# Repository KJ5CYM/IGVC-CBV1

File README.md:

# IGVC-CBV1
This is a failed project! The board as it stands does not work, due to my own amateur mistakes.

This board is the first step in a project to replace Arduino with custom hardware on the robot for the UT IGVC Team.
 
# Original Designers and Developers (2023)
Evan Eden, Colby McLane, Kerwin Zhang, Tarun Daggolu.

# Updates
Firmware is in developement and should surface within the coming weeks.

# 3D - View

# PCB

# Schematic

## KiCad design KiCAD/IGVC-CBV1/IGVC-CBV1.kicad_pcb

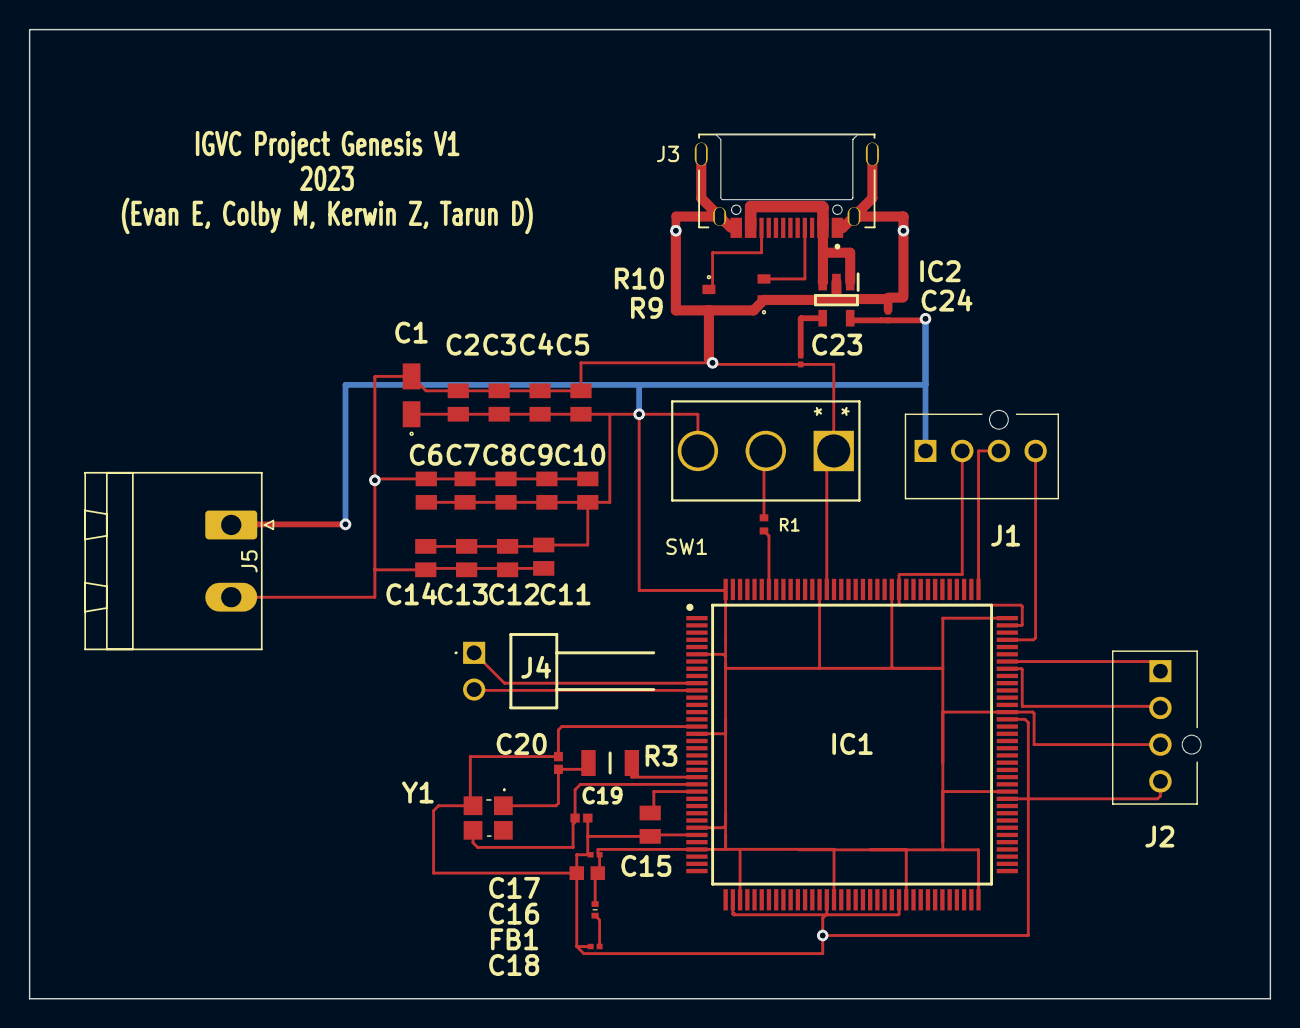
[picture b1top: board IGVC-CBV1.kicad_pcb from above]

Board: 2 copper layers, 85.9 x 67.1 mm, 36 parts (0 on the bottom side), 18 nets.

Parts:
C1: 10u; T491A
C2, C3, C4, C5, C6, C7, C8, C9, C10, C11, C12, C13, C14, C15: 100n; CAPC2012X140N
C16: 10n; CAPC17595_87N_KEM
C17, C18: 1u; CAPC0502X28N
C19, C20: 12 pF; CAPC1005X55N
C23: 1uF; CAPC0502X28N
C24: 1 uF; CAPC0502X28N
FB1: 120R; NFZ15SG152SN10B
IC1: STM32F407ZGT6; QFP50P2200X2200X160-144N
IC2: SPX3819M5-L-3-3_TR; SOT95P280X145-5N
J1: STLINKV2 PINS (2.54mm Pitch); 470531000
J2: Motor Driver Pins (2.54mm Pitch); 470531000
J3: 12401948E412A; AMPHENOL_12401948E412A
J4: Conn_01x02; 22122024
J5: Screw_Terminal_01x02; PhoenixContact_MSTBA_2,5_2-G_1x02_P5.00mm_Horizontal
R1: 10k; RESC1005X40N
R3: 60 Ohm; RESC3216X60N
R9, R10: 5K1; ERA3KV__0603_
SW1: SW_SPDT; 1101M2S3CQE2
Y1: EB2532YA12-25.000M_TR; EB2532YA1225000MTR

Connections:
+3.3V: C1.1, C2.1, C3.1, C4.1, C5.1, C6.1, C7.1, C8.1, C9.1, C10.1, C11.1, C12.1, C13.1, C14.1, C16.1, C17.1, C18.1, C24.1, FB1.1, FB1.2, IC1.6 (VBAT), IC1.17 (VDD_1), IC1.30 (VDD_2), IC1.33 (VDDA), IC1.39 (VDD_3), IC1.52 (VDD_4), IC1.62 (VDD_5), IC1.72 (VDD_6), IC1.84 (VDD_7), IC1.95 (VDD_8), IC1.108 (VDD_9), IC1.121 (VDD_10), IC1.131 (VDD_11), IC1.144 (VDD_12), IC2.5 (VOUT), J1.1, J2.3, J5.1, SW1.3 (C)
/BOOT0: IC1.138 (BOOT0), R1.2
/NRST: C15.1, IC1.25 (NRST)
/SW_BOOT0: R1.1, SW1.2 (B)
GND: C1.2, C2.2, C3.2, C4.2, C5.2, C6.2, C7.2, C8.2, C9.2, C10.2, C11.2, C12.2, C13.2, C14.2, C15.2, C16.2, C17.2, C18.2, C19.1, C20.1, C23.1, C24.2, IC1.16 (VSS_1), IC1.31 (VSSA), IC1.38 (VSS_2), IC1.51 (VSS_3), IC1.61 (VSS_4), IC1.83 (VSS_5), IC1.94 (VSS_6), IC1.107 (VSS_7), IC1.120 (VSS_8), IC1.130 (VSS_9), IC2.2 (GND), J1.2, J2.4, J3.A1_B12 (GND), J3.A12_B1 (GND), J3.S1 (SHELL_GND), J3.S2 (SHELL_GND), J3.S3 (SHELL_GND), J3.S4 (SHELL_GND), J5.2, R9.1, R10.2, SW1.1 (A), Y1.2 (COVER/GROUND)
I2C2_SCL: IC1.11 (PF1), J4.2
I2C2_SDA: IC1.10 (PF0), J4.1
unnamed: C23.2, IC2.4 (ADJ/BYP)
unnamed: J3.A5 (CC1), R9.2
unnamed: J3.B5 (CC2), R10.1
unnamed: C20.2, R3.1, Y1.1 (CRYSTAL_1)
RCC_OSC_IN: IC1.23 (PH0), R3.2
RCC_OSC_OUT: C19.2, IC1.24 (PH1), Y1.3 (CRYSTAL_2)
SWCLK: IC1.109 (PA14), J1.3
SWDIO: IC1.105 (PA13), J1.4
USART1_RX: IC1.102 (PA10), J2.1
USART1_TX: IC1.101 (PA9), J2.2
VBUS: IC2.1 (VIN), IC2.3 (EN), J3.A4_B9 (VBUS), J3.A9_B4 (VBUS)

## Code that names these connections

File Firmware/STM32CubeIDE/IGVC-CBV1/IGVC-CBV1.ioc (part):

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Mcu.Name=STM32F407Z(E-G)Tx
Mcu.Package=LQFP144
Mcu.UserName=STM32F407ZGTx
PA10.Mode=Asynchronous
PA10.Signal=USART1_RX
PA13.Mode=Serial_Wire
PA13.Signal=SYS_JTMS-SWDIO
PA14.Mode=Serial_Wire
PA14.Signal=SYS_JTCK-SWCLK
PA9.Mode=Asynchronous
PA9.Signal=USART1_TX
PF0.Mode=I2C
PF0.Signal=I2C2_SDA
PF1.Mode=I2C
PF1.Signal=I2C2_SCL
PH0-OSC_IN.Mode=HSE-External-Oscillator
PH0-OSC_IN.Signal=RCC_OSC_IN
PH1-OSC_OUT.Mode=HSE-External-Oscillator
PH1-OSC_OUT.Signal=RCC_OSC_OUT
RCC.HSE_VALUE=25000000
RCC.SYSCLKFreq_VALUE=168000000
RCC.SYSCLKSource=RCC_SYSCLKSOURCE_PLLCLK
board=custom

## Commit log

2023-09-29 Added initial schematic with cursed power setup
2023-09-29 STM32 symbol
2023-09-30 Cleaned up and have a basis for pin functions.
2023-10-01 Implemented Clock and STLink Header
    Also, defined our potential pins on the controller for I2C, UART, and such.
2023-10-03 8MB NOR Flash added to schematic with associated docs and files
2023-10-04 Fixed symbol tables...
2023-10-04 Setup project local directories for portability.
2023-10-04 Added MD Pins and Cleaned up.
2023-10-06 Arduino Pins
2023-10-07 Draft 5
2023-10-07 Schematic DONE!! PCB BEGINS!
2023-10-08 placed some things where they need to go
2023-10-08 finished layout
2023-10-13 Finished PCB Traces
2023-10-13 Somewhat Driver Structure.
2023-10-14 Update To Firmware
2023-10-15 PCB Update
2023-10-15 Added Screenshots
2023-10-15 Firmware Update
2023-10-17 Finishing Touches on PCB
2023-10-21 fixed names
2023-10-22 New MotorFIFO to Reevaluate for STM32.
2023-11-05 Fixed send_command error.
2023-11-22 Create LICENSE
